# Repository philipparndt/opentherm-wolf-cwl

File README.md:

# Wolf CWL OpenTherm Decoder

Decoder tool for analyzing OpenTherm protocol communication between a BM remote control and a Wolf CWL ventilation/heat-recovery unit. Built to reverse-engineer the protocol for building a custom ESP32-based controller.

## Usage

```bash
# Default: human-readable deduplicated output
decode <file.sal|file.csv>

# Verbose: raw hex, parity, bit-timing analysis
decode <file> --verbose

# Diff: compare two captures side by side, highlights changes
decode diff <baseline.sal> <changed.sal>
```

Supports Saleae Logic 2 captures (`.sal`) and CSV exports (`.csv`). SAL files are significantly faster to process.

## Findings

### Control Summary

Everything needed to control the Wolf CWL via OpenTherm:

| Function | Method |
|----------|--------|
| **Ventilation level** | Write-Data to ID 71, value 0-3 |
| **Bypass open** | Set bit 1 in HI byte of ID 70 Read-Data request |
| **Bypass close** | Clear bit 1 in HI byte of ID 70 Read-Data request |
| **Filter reset** | Set bit 4 in HI byte of ID 70 Read-Data request (reset filter timer after replacement) |
| **Read temperatures** | Read-Data ID 80 (supply inlet), ID 82 (exhaust inlet) |
| **Read ventilation %** | Read-Data ID 77 |
| **Read bypass state** | Check `ventilation` bit (bit 1 HI byte) in ID 70 response |
| **Read fault status** | ID 72 (`Fault flags/code V/H`) — the HI-byte `fault` bit in ID 70 is *not* reliable on Wolf CWL, see notes below |
| **Read filter status** | Check **bit 5 of the LO byte** in ID 70 response (Wolf OEM use of a spec-reserved slave-status bit; the response HI byte is only an echo of the master flags) |

### Supported OpenTherm Data IDs

The Wolf CWL (tested with CWL Excellent, BM remote control as master) responds to the following data IDs:

| Data ID | Name | Type | Direction | Description |
|---------|------|------|-----------|-------------|
| 2 | Master configuration | config/member-id | Write | Master flags=0x00, member-id=18 |
| 70 | Status V/H | flag8 | Read | Bidirectional: master sends control flags, slave returns status |
| 71 | Control setpoint V/H | u8 | Write | Ventilation level (0-3) |
| 72 | Fault flags/code V/H | flag8 | Read | Fault flags + OEM fault code |
| 74 | Config/member-ID V/H | config/member-id | Read | Slave flags=0x07, member-id=0 |
| 77 | Relative ventilation | u8 (%) | Read | Current ventilation percentage |
| 80 | Supply inlet temperature | f8.8 (°C) | Read | Fresh air intake temperature |
| 82 | Exhaust inlet temperature | f8.8 (°C) | Read | Room exhaust temperature |
| 89 | TSP index/value V/H | tsp | Read | Transparent Slave Parameters (see below) |
| 126 | Master product version | version | Write | type=18 version=2 |
| 127 | Slave product version | version | Read | type=0 version=0 (CWL does not respond) |

### Status V/H (ID 70) — Bidirectional Control

The Status V/H exchange carries control flags in **both directions**. This is the key mechanism for bypass control.

**Master → Slave (HI byte of Read-Data request):**

| Bit | Name | Description |
|-----|------|-------------|
| 0 | ch | Central heating / ventilation enable |
| 1 | **bypass** | **Bypass damper control: 1=open, 0=closed** |
| 2 | cooling | Cooling enable (if cooling register installed) |
| 3 | dhw | DHW enable |
| 4 | filter | Filter timer reset (set briefly after filter replacement) |
| 5 | diag | Diagnostics request |

**Slave → Master (Read-Ack response):**

The **HI byte of the Read-Ack is an echo of the master status flags** from the request — it carries no slave state. (Earlier revisions of this document interpreted it as a slave status byte and described a "permanently latched fault bit"; that was our own always-set ventilation-enable bit coming back.)

The actual slave status is the **LO byte**, laid out as in the OpenTherm V/H spec:

| Bit | Name | Description |
|-----|------|-------------|
| 0 | fault | Fault indication |
| 1 | ventilation | Ventilation mode active |
| 2 | bypass | Bypass status (1 = open) |
| 3 | bypass auto | Bypass automatic mode |
| 4 | free vent | Free ventilation status |
| 5 | **filter** | **Filter replacement required (1 = service due, 0 = OK).** Reserved in the spec; used by Wolf (Brink Renovent / Viessmann Vitovent OEM siblings) as the filter-check bit. |
| 6 | diag | Diagnostic indication |

Bit 5 was confirmed in `FIL_CLEAN.sal`, which captures the live transition during a filter-reset: LO went from `0x26` → `0x06` (bit 5 cleared) while HI stayed at `0x03` and ID 72 (Fault flags/code) stayed at `0x0000` throughout.

> **Do not derive filter status from ID 72.** An OEM fault code of 6 was once assumed to mean "filter dirty" (FIL2 hypothesis), but a live unit was observed reporting ID 72 = `0x0006` together with LO bit 6 (diagnostic indication) while the filter was clean and the CWL display showed no FIL — code 6 is a diagnostic status code, not the filter message. LO bit 5 is the only reliable filter signal.

The bypass is controlled by setting/clearing **bit 1 of the HI byte** in every Status V/H request; the actual damper state is reported in LO bit 2 (and TSP 54).

### Ventilation Level Control

Ventilation level is controlled via **Data ID 71** (Control setpoint V/H). The mapping is:

| Setpoint value | Mode | Relative ventilation (ID 77) |
|---------------|------|------------------------------|
| 0 | Off | 0% |
| 1 | Reduced | 51% |
| 2 | Normal | 67% |
| 3 | Party | 100% |

The `fault` bit in Status V/H (ID 70) may toggle briefly during mode transitions. This appears to be a transient state, not an actual fault indication.

### TSP Register Map

The BM remote cycles through TSP registers via Data ID 89, reading one index per polling cycle (~11 seconds per cycle). A full TSP scan takes approximately 5-6 minutes (31 indices).

TSP values did **not** change when switching ventilation levels or toggling bypass. Ventilation is controlled via ID 71, bypass via ID 70. TSPs hold configuration and live diagnostic data.

The Wolf CWL is OEM-identical to the **Brink Renovent HR** and **Viessmann Vitovent 300**. The TSP register map from the [Brink Renovent OpenTherm project](https://github.com/raf1000/brink_openhab) applies directly.

Many indices come in even/odd pairs for 16-bit values (even=LO, odd=HI byte).

#### Airflow Configuration (m³/h)

| TSP Index | Brink name | Value | Description |
|-----------|------------|-------|-------------|
| 0, 1 | U1 | 100, 0 | Airflow rate step 1 (Reduced): **100 m³/h** |
| 2, 3 | U2 | 130, 0 | Airflow rate step 2 (Normal): **130 m³/h** |
| 4, 5 | U3 | 195, 0 | Airflow rate step 3 (Party): **195 m³/h** |

#### Bypass & Temperature Settings

| TSP Index | Brink name | Value | Description |
|-----------|------------|-------|-------------|
| 6 | U4 | 20 | Bypass min. outdoor temp (value ÷ 2 = °C → **10 °C**). Bypass only opens when outdoor air ≥ this temperature. |
| 7 | U5 | 44 | Bypass min. indoor temp (value ÷ 2 = °C → **22 °C**). Bypass only opens when indoor air ≥ this temperature. |

#### Configuration Parameters

| TSP Index | Brink name | Value | Description |
|-----------|------------|-------|-------------|
| 11 | I1 | 100 | Fixed imbalance (value shifted by 100, so 100 = **0% imbalance**) |
| 17 | I7 | 1 | Pressure control / fan mode setting |
| 18 | I8 | 1 | Bypass configuration |
| 19 | I9 | 2 | Hysteresis / preheater setting |
| 20 | I10 | 0 | Additional config |
| 23 | I13 | 1 | Filter message setting |
| 24 | I14 | 0 | PCB configuration |
| 48, 49 | P18 | 193, 0 | Device/PCB config flags |

#### Live / Status Values (read-only, change during operation)

| TSP Index | Brink name | Value range | Description |
|-----------|------------|-------------|-------------|
| 52, 53 | CurrentVol | 100-130, 0 | Current outlet volume **[m³/h]** |
| 54 | BypassStatus | 1 | Bypass valve position (0=shut, 1=auto, 2=open?) |
| 55 | TempAtmo | 114-118 | Atmospheric temperature (value − 100 = °C, so 114 → **14 °C**) |
| 56 | TempIndoors | 121 | Indoor temperature (value − 100 = °C, so 121 → **21 °C**) |
| 60, 61 | — | 0-130, 0 | Changes within captures — possibly supply/exhaust flow |
| 62, 63 | CurrentOutputVol | 100-113, 0 | Current output volume **[m³/h]** |
| 64, 65 | CPID | 20-215, 0-1 | Input duct pressure **[Pa]** |
| 66, 67 | CPOD | 196-255, 0 | Output duct pressure **[Pa]** |
| 68 | FrostStatus | 0 | Frost protection status (0 = no frost) |

### Data IDs to Probe

The BM remote only polls a subset of the available V/H data IDs. The following IDs are defined in the OpenTherm V/H spec and may be supported by the CWL, but have not been tested yet. Probe these with the ESP32 firmware to discover additional sensors:

| Data ID | Name | Type | Notes |
|---------|------|------|-------|
| 78 | Relative humidity exhaust | u8 (%) | Humidity sensor (if installed) |
| 79 | CO2 level exhaust | u16 (ppm) | CO2/VOC sensor (if installed) |
| 81 | Supply outlet temperature | f8.8 (°C) | Temperature after heat recovery |
| 83 | Exhaust outlet temperature | f8.8 (°C) | Temperature after heat recovery |
| 84 | Exhaust fan speed | u16 (rpm) | Fan speed diagnostics |
| 85 | Supply fan speed | u16 (rpm) | Fan speed diagnostics |
| 87 | Nominal ventilation value | u8 | Configured nominal airflow |
| 88 | TSP count V/H | u8 | Total number of TSP registers supported |

If the CWL supports a data ID, it will respond with Read-Ack. If not, it will either not respond or send Unknown-DataId.

### Polling Cycle

The BM remote polls the CWL in a fixed cycle of approximately 11 seconds containing:

1. Master configuration (ID 2) — Write-Data
2. Status V/H (ID 70) — Read-Data with master control flags
3. Control setpoint V/H (ID 71) — Write-Data
4. Config/member-ID V/H (ID 74) — Read-Data
5. Relative ventilation (ID 77) — Read-Data
6. Supply inlet temperature (ID 80) — Read-Data
7. Exhaust inlet temperature (ID 82) — Read-Data
8. Master product version (ID 126) — Write-Data
9. Slave product version (ID 127) — Read-Data (no response from CWL)
10. TSP index/value V/H (ID 89) — Read-Data, rotates through different index each cycle
11. Fault flags/code V/H (ID 72) — Read-Data (sometimes included)

## ESP32 Firmware Guide

The firmware serves a web UI with live status and a 24 h history view — supply/exhaust temperatures, indoor/outdoor humidity and enthalpy, bypass state, and ventilation level changes annotated with the reason for each switch:

### Minimal Polling Loop

To replicate the BM's communication, the ESP32 firmware should send these requests in a loop (~1 second between each):

```
1. Write-Data  ID=2   value=0x0012        (master config: member-id=18)
2. Read-Data   ID=70  value=0x0N00        (status: HI byte = control flags, N = bypass bit)
3. Write-Data  ID=71  value=0x000L        (ventilation level: L = 0-3)
4. Read-Data   ID=74  value=0x0000        (read config/member-id)
5. Read-Data   ID=77  value=0x0000        (read relative ventilation %)
6. Read-Data   ID=80  value=0x0000        (read supply inlet temp)
7. Read-Data   ID=82  value=0x0000        (read exhaust inlet temp)
8. Read-Data   ID=89  value=0xII00        (read TSP index II)
```

### Bypass Control

In step 2, set the HI byte of the request value:
- `0x0100` — bypass closed, ventilation enabled (ch=on)
- `0x0300` — bypass open, ventilation enabled (ch=on, bypass=on)

The slave response HI byte confirms the state:
- Bit 0: fault
- Bit 1: ventilation/bypass active

### Ventilation Levels

In step 3, set the LO byte:
- `0x0000` — Off (0%)
- `0x0001` — Reduced (51%)
- `0x0002` — Normal (67%)
- `0x0003` — Party (100%)

## Hardware

### Capture Setup (passive analysis)

- **Saleae Logic 2** analyzer tapping the OpenTherm bus between BM remote and CWL unit
- Analog capture at 1.5625 MHz sample rate
- OpenTherm signal: Manchester encoded at ~1000 baud
- Request (master→slave): ~10.8V peak
- Response (slave→master): ~7.3V peak

### Controller Hardware

- **DIYLess Master OpenTherm Shield** — handles OpenTherm electrical signaling
- **ESP32** (e.g. WeMos D1 mini ESP32) — runs custom firmware
- **[ihormelnyk/opentherm_library](https://github.com/ihormelnyk/opentherm_library)** — Arduino library for OpenTherm master communication

The DIYLess shield acts as the OpenTherm master, replacing the BM remote control. The ESP32 can then:
- Read all sensor values (temperatures, ventilation %, status, faults)
- Set ventilation level by writing to Data ID 71 (values 0-3)
- Control bypass via Status V/H (ID 70) master flags
- Read TSP registers for diagnostics
- Publish data via MQTT to Home Assistant (see [docs/mqtt-topics.md](docs/mqtt-topics.md) for the full topic reference)

### ESPHome Compatibility

The official ESPHome OpenTherm component does **not** support V/H (ventilation/heat-recovery) data IDs 70-91. It only supports boiler/heating control. A custom firmware is required for the Wolf CWL.

## Building

```bash
cd decode
go build -o decode .
```

Requires Go 1.26+.

## Schedules

Weekday schedule:
```
0:00 - 8:00 reduced
8:00 - 13:00 normal
13:00 - 15:00 reduced
15:00 - 18:00 normal
18:00 - 0:00 reduced
```

Weekend schedule:
```
0:00 - 10:00 reduced
10:00 - 13:00 normal
13:00 - 15:00 reduced
15:00 - 18:30 normal
```

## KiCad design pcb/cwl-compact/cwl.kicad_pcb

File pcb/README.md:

# Wolf CWL Controller — Shield PCB

Shield board that stacks on top of an [Olimex ESP32-POE](https://www.olimex.com/Products/IoT/ESP32/ESP32-POE/open-source-hardware) via the UEXT connector. Provides the OpenTherm interface, OLED display, and rotary encoder.

## UEXT Connector Pinout (ESP32-POE)

The [UEXT](https://www.olimex.com/Products/Modules/UEXT/) is a 10-pin 2x5 box header (2.54 mm pitch) providing I²C, SPI, and UART:

| UEXT Pin | Signal | ESP32 GPIO | Used For |
|----------|--------|------------|----------|
| 1  | 3.3V | —       | Power |
| 2  | GND  | —       | Ground |
| 3  | TXD  | GPIO 4  | OpenTherm TX (via SB3) |
| 4  | RXD  | GPIO 36 | OpenTherm RX (via SB4) |
| 5  | SCL  | GPIO 16 | OLED Display |
| 6  | SDA  | GPIO 13 | OLED Display |
| 7  | MISO | GPIO 15 | Encoder CLK |
| 8  | MOSI | GPIO 2  | Status LED |
| 9  | SCK  | GPIO 14 | Encoder DT |
| 10 | SS   | GPIO 5  | Encoder SW |

## Variants

| Variant | Project | Notes |
|---------|---------|-------|
| `cwl` (default) | `cwl/cwl.kicad_pro` | Main board. Melnyk-topology on-board OpenTherm front-end. Combined OLED footprint accepts either a 0.96″ or 1.3″ SH1106 module. |
| `cwl-diyless` | `cwl-diyless/cwl.kicad_pro` | Off-board OpenTherm interface via a DIYless D1-mini shield. Separate J3 / J3B footprints for the two OLED sizes. |

## Bill of Materials (`cwl`)

| Ref | Part | Value / Mfr P/N | Footprint | Symbol | Mouser # | Qty |
|-----|------|-----------------|-----------|--------|----------|-----|
| J1 | UEXT 2×5 IDC socket | HIF3FB-10DA-2.54DSA(69) (Hirose) | `IDC:IDC-Stecker_2x05_P2.54mm_Vertical` | `Connector_Generic:Conn_02x05_Odd_Even` | 798-HIF3FB10DA254D69 | 1 |
| J2 | Screw terminal, 2-pos 5.08 mm | MKDS 1,5/2-5,08 (Phoenix Contact) | `TerminalBlock_Phoenix:TerminalBlock_Phoenix_MKDS-1,5-2-5.08_1x02_P5.08mm_Horizontal` | `Connector:Conn_01x02_Pin` | 651-1729018 | 1 |
| J3 | OLED header (0.96″ + 1.3″ combined) | 4-pin header (use module's own header) | `SSD1306:128x64OLED-MountingHoles-Combined` | `Connector:Conn_01x04_Pin` | — | 1 |
| U1, U2 | Optocoupler, SOIC-4 | LTV-817S-B (Lite-On) | `Package_SO:SOP-4_7.5x4.1mm_P2.54mm` | `Isolator:PC817` | 859-LTV-817S-B | 2 |
| Q1 | PNP BJT, SOT-23 | BC858A or BC858B (Nexperia) | `Package_TO_SOT_SMD:SOT-23` | `Transistor_BJT:BC858` | 771-BC858A,215 | 1 |
| D1–D4 | Switching diode, SOD-323 | 1N4148WS (Vishay) | `Diode_SMD:D_SOD-323` | `Device:D` | 78-1N4148WS-HG3_A-08 | 4 |
| D5 | 4.7 V zener, SOD-123, 500 mW | BZT52C4V7 (Vishay) | `Diode_SMD:D_SOD-123` | `Device:D_Zener` | 78-BZT52C4V7-E3-08 | 1 |
| D6 | 15 V zener, SOD-123, 500 mW | BZT52C15 (Vishay) | `Diode_SMD:D_SOD-123` | `Device:D_Zener` | 78-BZT52C15-E3-08 | 1 |
| D7 | 4.3 V zener, SOD-123, 500 mW | BZT52C4V3 (Vishay) | `Diode_SMD:D_SOD-123` | `Device:D_Zener` | 78-BZT52C4V3-E3-08 | 1 |
| R1, R4 | 330 Ω, 0603, 1 % | RC0603FR-07330RL (Yageo) | `Resistor_SMD:R_0603_1608Metric` | `Device:R` | 603-RC0603FR-07330RL | 2 |
| R2 | 220 Ω, 0603, 1 % | RC0603FR-07220RL (Yageo) | `Resistor_SMD:R_0603_1608Metric` | `Device:R` | 603-RC0603FR-07220RL | 1 |
| R3 | 100 Ω, 0603, 1 % | RC0603FR-07100RL (Yageo) | `Resistor_SMD:R_0603_1608Metric` | `Device:R` | 603-RC0603FR-07100RL | 1 |
| R5 | 1.5 kΩ, 0603, 1 % | RC0603FR-071K5L (Yageo) | `Resistor_SMD:R_0603_1608Metric` | `Device:R` | 603-RC0603FR-071K5L | 1 |
| R6, R7 | 10 kΩ, 0603, 1 % | RC0603FR-0710KL (Yageo) | `Resistor_SMD:R_0603_1608Metric` | `Device:R` | 603-RC0603FR-0710KL | 2 |
| R8 | 1 kΩ, 0603, 1 % | RC0603FR-071KL (Yageo) | `Resistor_SMD:R_0603_1608Metric` | `Device:R` | 603-RC0603FR-071KL | 1 |
| SW1 | Rotary encoder w/ switch | EC12E2424407 (Alps Alpine) | `Rotary_Encoder:RotaryEncoder_Alps_EC12E-Switch_Vertical_H20mm` | `Device:RotaryEncoder_Switch` | — | 1 |
| LED1 | Green LED, 0805 | SML-LXT0805GW-TR (Lumex) | `LED_SMD:LED_0805_2012Metric` | `Device:LED` | 696-SML-LXT0805GW | 1 |
| MH1–MH4 | M3 mounting hole, GND-tied | — | `MountingHole:MountingHole_3.2mm_M3_Pad_Via` | `Mechanical:MountingHole_Pad` | — | 4 |
| SB3, SB4 | UEXT TX/RX → OT routing bridges (etched into board, no part) | — | `Jumper:SolderJumper-2_P1.3mm_Bridged_RoundedPad1.0x1.5mm` | `Jumper:SolderJumper_2_Bridged` | — | — |
| — | 0.96″ SH1106 OLED module, I²C, 4-pin | — | — | — | (Amazon / AliExpress) | 1 (pick one) |
| — | 1.3″ SH1106 OLED module, I²C, 4-pin | — | — | — | (Amazon / AliExpress) | 1 (pick one) |

## Build targets

```
make generate-3d      # regenerate the local STEP models in 3dmodels/
make export-stl-full  # full PCB assembly STL (VARIANT=cwl by default)
make export-stl-print # version with floating IDC socket for 3D printing
make export-stl-board # bare PCB only
make export-stl-parts # components only (no board)
make gerber           # Gerbers + drills (zipped)
make plot-pdf         # front + back assembly PDFs
make ibom             # Interactive HTML BOM (needs InteractiveHtmlBom plugin)
make clean            # remove generated artifacts
```

Set `VARIANT=cwl-diyless` to target the diyless project instead.

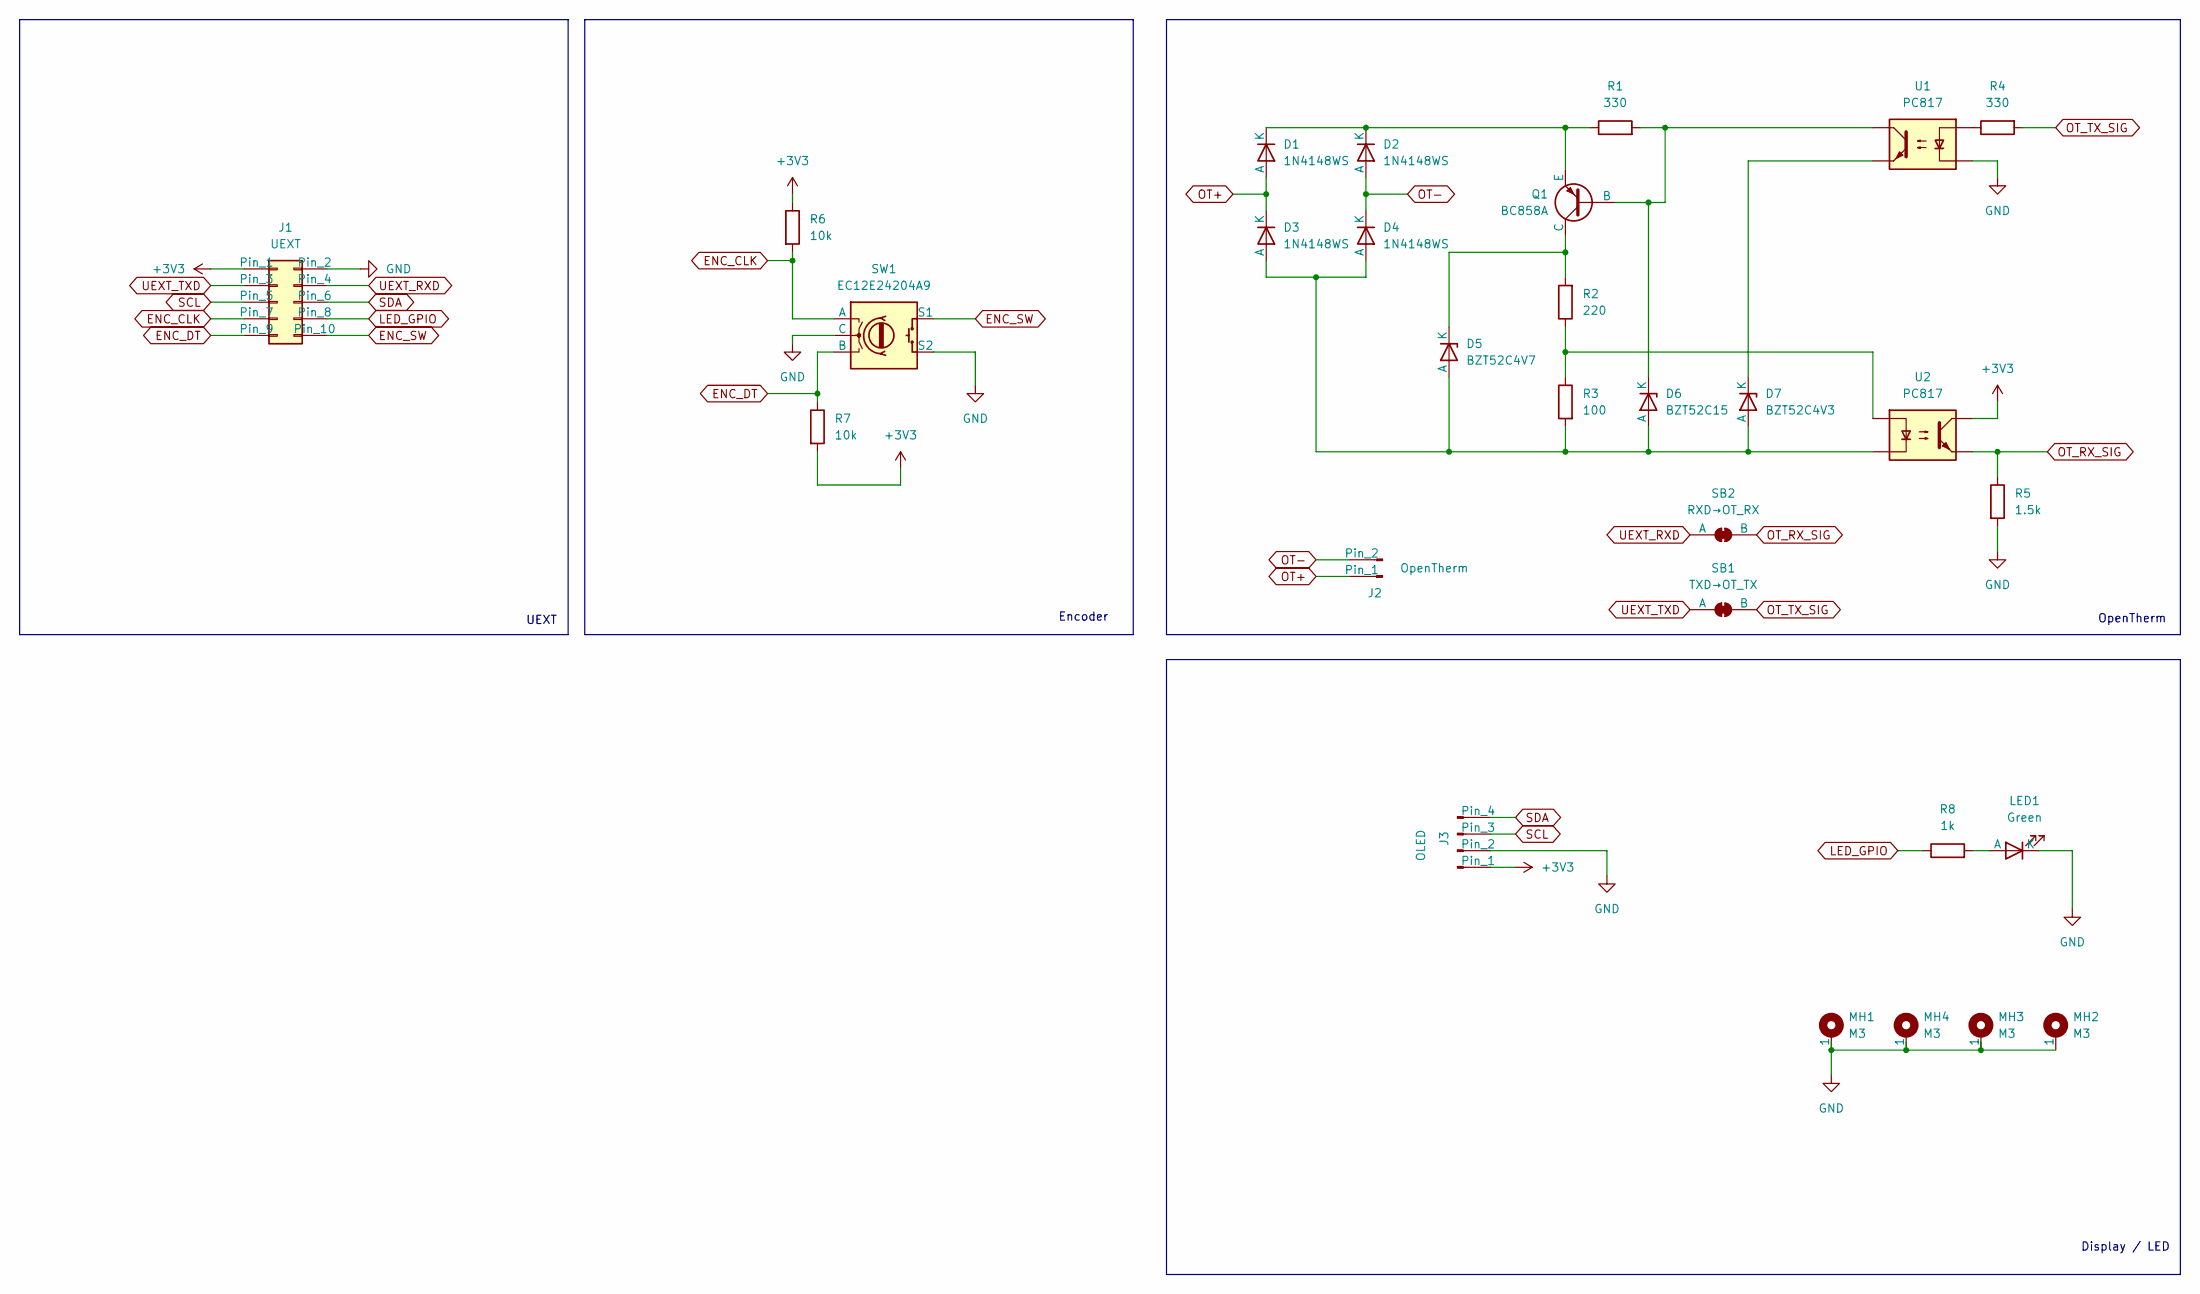
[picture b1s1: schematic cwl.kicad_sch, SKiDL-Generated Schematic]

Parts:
D1, D2, D3, D4: 1N4148WS; D_SOD-323
D5: BZT52C4V7; D_SOD-123
D6: BZT52C15; D_SOD-123
D7: BZT52C4V3; D_SOD-123
J1: UEXT; IDC-Stecker_2x05_P2.54mm_Vertical; LCSC C358738
J2: OpenTherm; TerminalBlock_Phoenix_MKDS-1,5-2-5.08_1x02_P5.08mm_Horizont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
J3: OLED; 128x64OLED-MountingHoles-Combined
LED1: Green; LED_0805_2012Metric; LCSC C2297
MH1, MH2, MH3, MH4: M3; MountingHole_3.2mm_M3_Pad_Via
Q1: BC858A; SOT-23
R1, R4: 330; R_0603_1608Metric; LCSC C23138
R2: 220; R_0603_1608Metric; LCSC C22962
R3: 100; R_0603_1608Metric; LCSC C22775
R5: 1.5k; R_0603_1608Metric; LCSC C22843
R6, R7: 10k; R_0603_1608Metric; LCSC C25804
R8: 1k; R_0603_1608Metric; LCSC C21190
SB1: TXD→OT_TX; SolderJumper-2_P1.3mm_Bridged_RoundedPad1.0x1.5mm
SB2: RXD→OT_RX; SolderJumper-2_P1.3mm_Bridged_RoundedPad1.0x1.5mm
SW1: EC12E24204A9; RotaryEncoder_Alps_EC12E-Switch_Vertical_H20mm
U1, U2: PC817; SOP-4_7.5x4.1mm_P2.54mm

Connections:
+3V3: J1.1, J3.1, R6.1, R7.2, U2.4
ENC_CLK: J1.7, R6.2, SW1.A
ENC_DT: J1.9, R7.1, SW1.B
ENC_SW: J1.10, SW1.S1
GND: J1.2, J3.2, LED1.1 (K), MH1.1 (1_1), MH2.1 (1_1), MH3.1 (1_1), MH4.1 (1_1), R5.2, SW1.C, SW1.MP, SW1.S2, U1.2
LED_GPIO: J1.8, R8.1
unnamed: D1.1 (K), D2.1 (K), Q1.2 (E), R1.1
unnamed: D3.2 (A), D4.2 (A), D5.2 (A), D6.2 (A), D7.2 (A), R3.2, U2.2
unnamed: D5.1 (K), Q1.3 (C), R2.2
unnamed: D6.1 (K), Q1.1 (B), R1.2, U1.4
unnamed: D7.1 (K), U1.3
unnamed: LED1.2 (A), R8.2
unnamed: R2.1, R3.1, U2.1
unnamed: R4.1, U1.1
OT+: D1.2 (A), D3.1 (K), J2.1
OT-: D2.2 (A), D4.1 (K), J2.2
OT_RX_SIG: R5.1, SB2.2 (B), U2.3
OT_TX_SIG: R4.2, SB1.2 (B)
SCL: J1.5, J3.3
SDA: J1.6, J3.4
UEXT_RXD: J1.4, SB2.1 (A)
UEXT_TXD: J1.3, SB1.1 (A)

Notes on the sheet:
UEXT
OpenTherm
Display / LED
Encoder

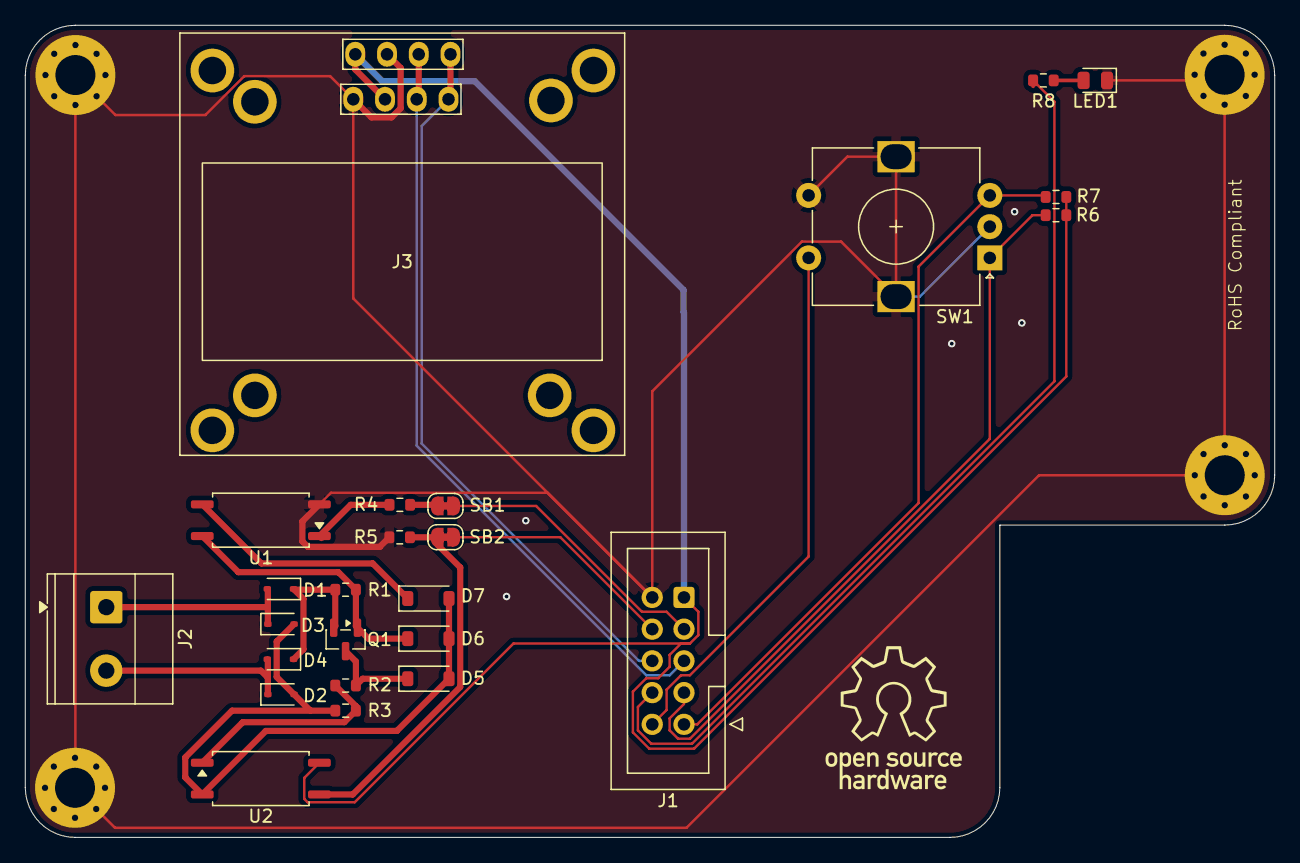
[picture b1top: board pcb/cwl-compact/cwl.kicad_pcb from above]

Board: 2 copper layers, 100.0 x 65.0 mm, 29 parts (0 on the bottom side), 22 nets.

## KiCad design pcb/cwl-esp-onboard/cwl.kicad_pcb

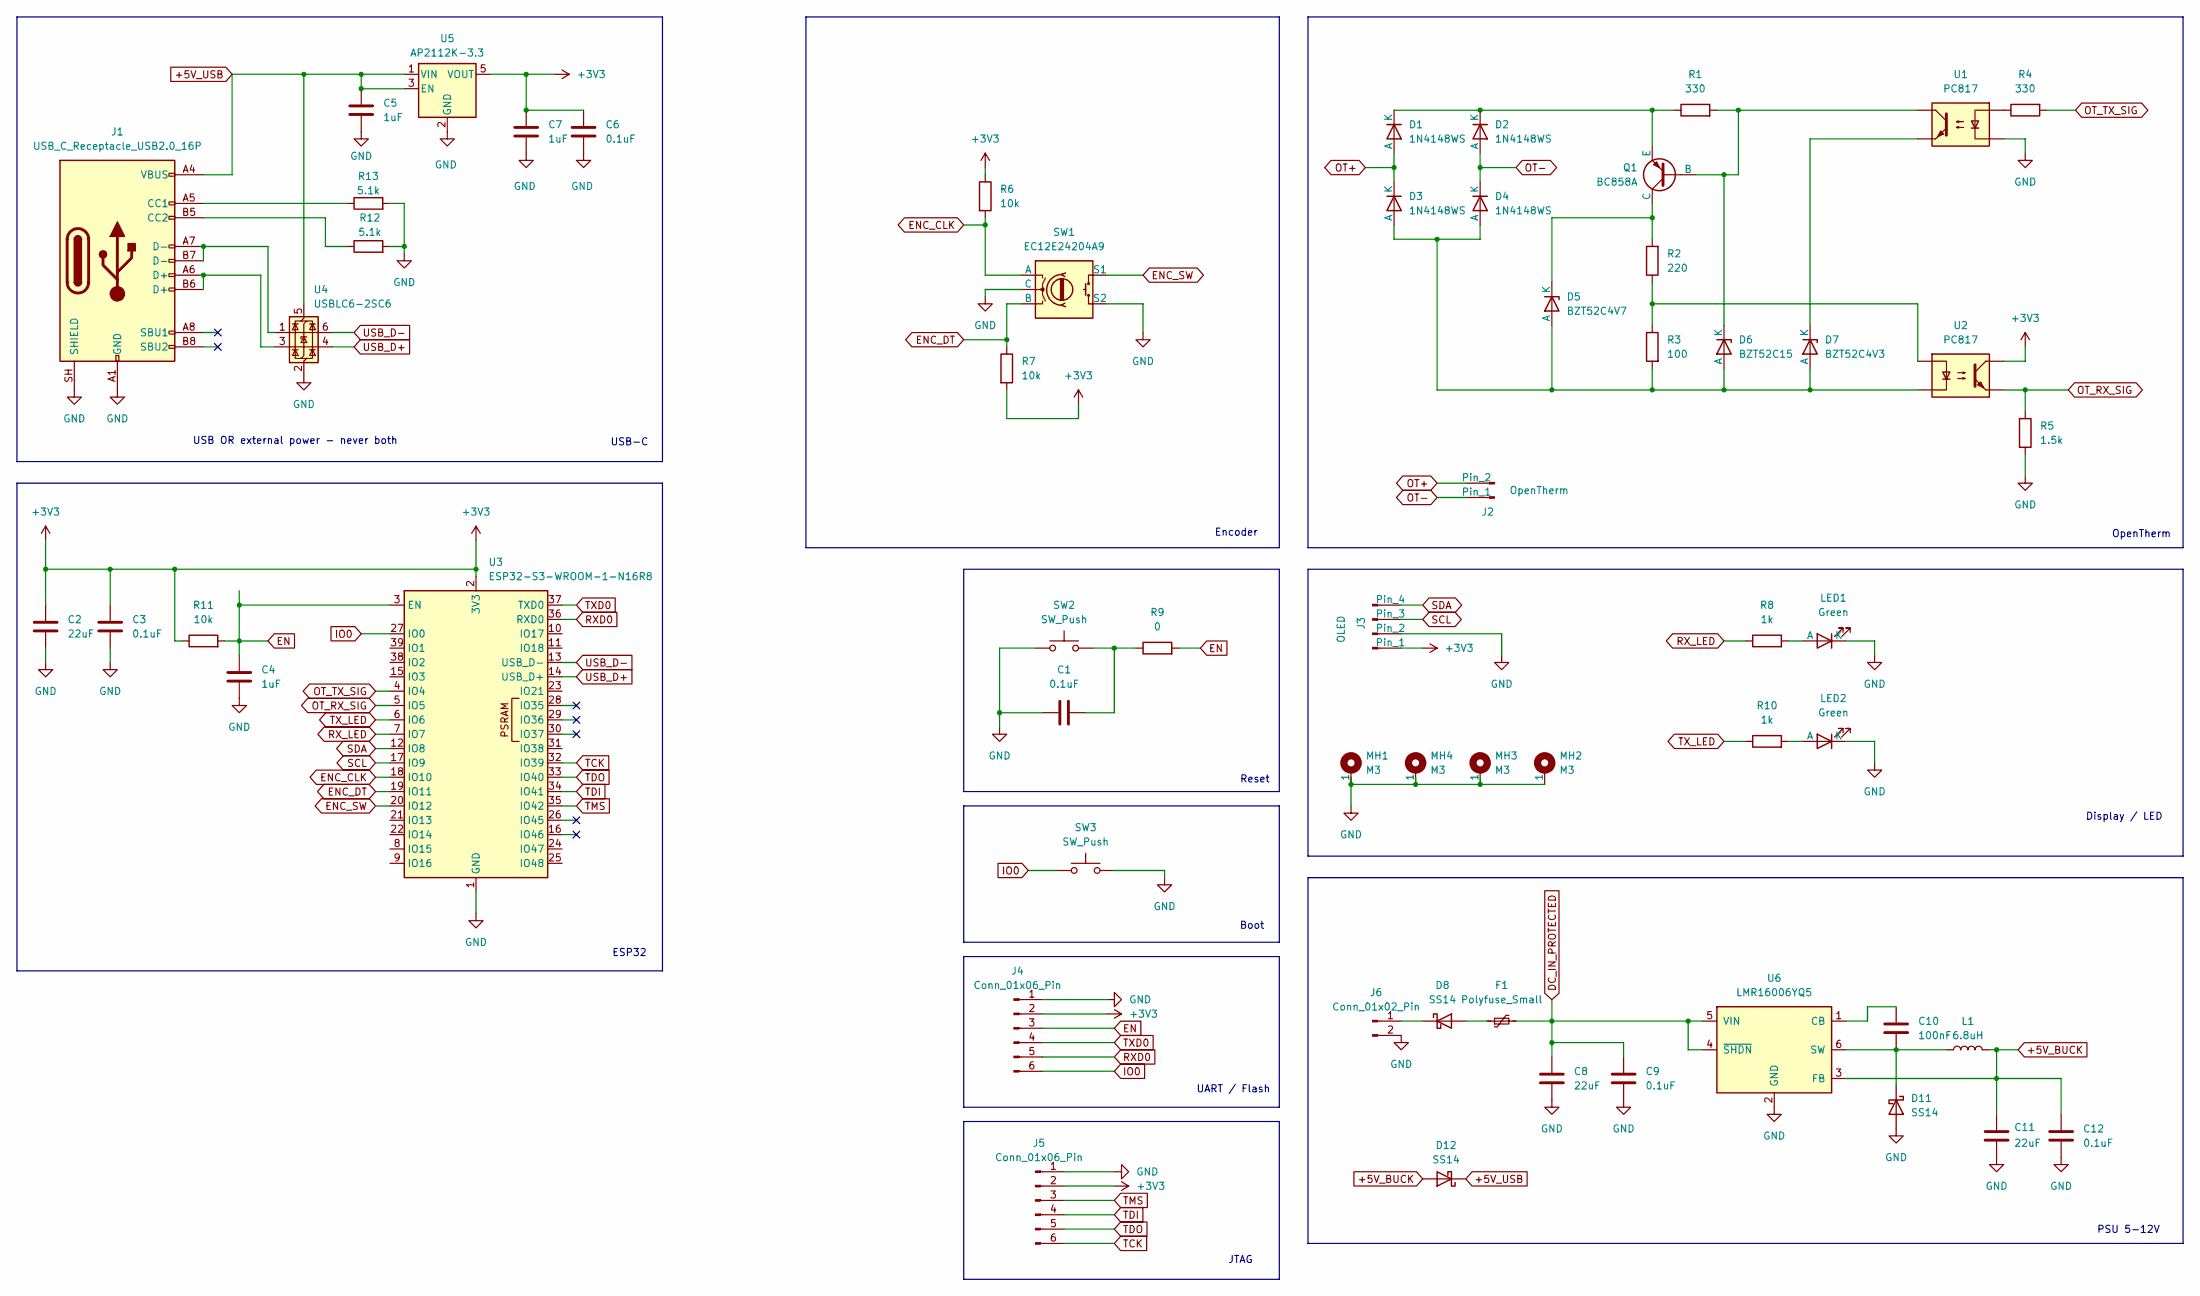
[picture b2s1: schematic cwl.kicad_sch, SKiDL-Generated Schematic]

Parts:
C1, C3, C6, C9, C12: 0.1uF; C_0402_1005Metric
C2, C8, C11: 22uF; C_1210_3225Metric
C4, C5, C7: 1uF; C_0402_1005Metric
C10: 100nF; C_0402_1005Metric
D1, D2, D3, D4: 1N4148WS; D_SOD-323
D5: BZT52C4V7; D_SOD-123
D6: BZT52C15; D_SOD-123
D7: BZT52C4V3; D_SOD-123
D8, D11, D12: SS14; D_SMA
F1: Polyfuse_Small; Fuse_1812_4532Metric
J1: USB_C_Receptacle_USB2.0_16P; USB_C_Receptacle_HRO_TYPE-C-31-M-12
J2: OpenTherm; TerminalBlock_Phoenix_MKDS-1,5-2-5.08_1x02_P5.08mm_Horizont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
J3: OLED; 128x64OLED-MountingHoles-Combined
J4: Conn_01x06_Pin; PinHeader_1x06_P2.54mm_Vertical
J5: Conn_01x06_Pin; PinHeader_1x06_P1.27mm_Vertical_SMD_Pin1Left
J6: Conn_01x02_Pin; TerminalBlock_Phoenix_MKDS-1,5-2-5.08_1x02_P5.08mm_Horizont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
L1: 6.8uH; L_6.3x6.3_H3
LED1, LED2: Green; LED_0805_2012Metric
MH1, MH2, MH3, MH4: M3; MountingHole_3.2mm_M3_Pad_Via
Q1: BC858A; SOT-23
R1, R4: 330; R_0603_1608Metric
R2: 220; R_0603_1608Metric
R3: 100; R_0603_1608Metric
R5: 1.5k; R_0603_1608Metric
R6, R7: 10k; R_0603_1608Metric
R8, R10: 1k; R_0603_1608Metric
R9: 0; R_0402_1005Metric
R11: 10k; R_0402_1005Metric
R12, R13: 5.1k; R_0402_1005Metric
SW1: EC12E24204A9; RotaryEncoder_Alps_EC12E-Switch_Vertical_H20mm
SW2, SW3: SW_Push; SW_SPST_TL3342
U1, U2: PC817; SOP-4_7.5x4.1mm_P2.54mm
U3: ESP32-S3-WROOM-1-N16R8; ESP32-S3-WROOM-1
U4: USBLC6-2SC6; SOT-23-6
U5: AP2112K-3.3; SOT-23-5
U6: LMR16006YQ5; SOT-23-6

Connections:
+3V3: C2.1, C3.1, C6.1, C7.1, J3.1, J4.2, J5.2, R6.1, R7.2, R11.1, U2.4, U3.2 (3V3), U5.5 (VOUT); also elsewhere on the board
+5V_BUCK: C11.1, C12.1, D12.2 (A), L1.2, U6.3 (FB)
+5V_USB: C5.1, D12.1 (K), J1.A4 (VBUS), J1.A9 (VBUS), J1.B4 (VBUS), J1.B9 (VBUS), U4.5 (VBUS), U5.1 (VIN), U5.3 (EN)
EN: C4.2, J4.3, R9.2, R11.2, U3.3 (EN)
ENC_CLK: R6.2, SW1.A, U3.18 (IO10); also elsewhere on the board
ENC_DT: R7.1, SW1.B, U3.19 (IO11); also elsewhere on the board
ENC_SW: SW1.S1, U3.20 (IO12); also elsewhere on the board
IO0: J4.6, SW3.1, U3.27 (IO0)
unnamed: C1.2, R9.1, SW2.2
unnamed: D1.1 (K), D2.1 (K), Q1.2 (E), R1.1
unnamed: D3.2 (A), D4.2 (A), D5.2 (A), D6.2 (A), D7.2 (A), R3.2, U2.2
unnamed: D5.1 (K), Q1.3 (C), R2.2
unnamed: D6.1 (K), Q1.1 (B), R1.2, U1.4
unnamed: D7.1 (K), U1.3
unnamed: D8.2 (A), F1.1
unnamed: D8.1 (K), J6.1
unnamed: J1.A5 (CC1), R13.1
unnamed: J1.B5 (CC2), R12.1
unnamed: J1.A6 (D+), J1.B6 (D+), U4.3 (I/O2)
unnamed: J1.A7 (D-), J1.B7 (D-), U4.1 (I/O1)
unnamed: LED1.2 (A), R8.2
unnamed: LED2.2 (A), R10.2
unnamed: R2.1, R3.1, U2.1
unnamed: R4.1, U1.1
OT+: D1.2 (A), D3.1 (K), J2.2
OT-: D2.2 (A), D4.1 (K), J2.1
OT_RX_SIG: R5.1, U2.3, U3.5 (IO5); also elsewhere on the board
OT_TX_SIG: R4.2, U3.4 (IO4); also elsewhere on the board
RXD0: J4.5, U3.36 (RXD0)
RX_LED: R8.1, U3.7 (IO7)
SCL: J3.3, U3.17 (IO9); also elsewhere on the board
SDA: J3.4, U3.12 (IO8); also elsewhere on the board
TCK: J5.6, U3.32 (IO39)
TDI: J5.4, U3.34 (IO41)
TDO: J5.5, U3.33 (IO40)
TMS: J5.3, U3.35 (IO42)
TXD0: J4.4, U3.37 (TXD0)
TX_LED: R10.1, U3.6 (IO6)
USB_D+: U3.14 (USB_D+), U4.4 (I/O2)
USB_D-: U3.13 (USB_D-), U4.6 (I/O1)

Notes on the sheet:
Boot
USB-C
Reset
PSU 5-12V
OpenTherm
UART / Flash
ESP32
JTAG
Display / LED
Encoder
USB OR external power - never both

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
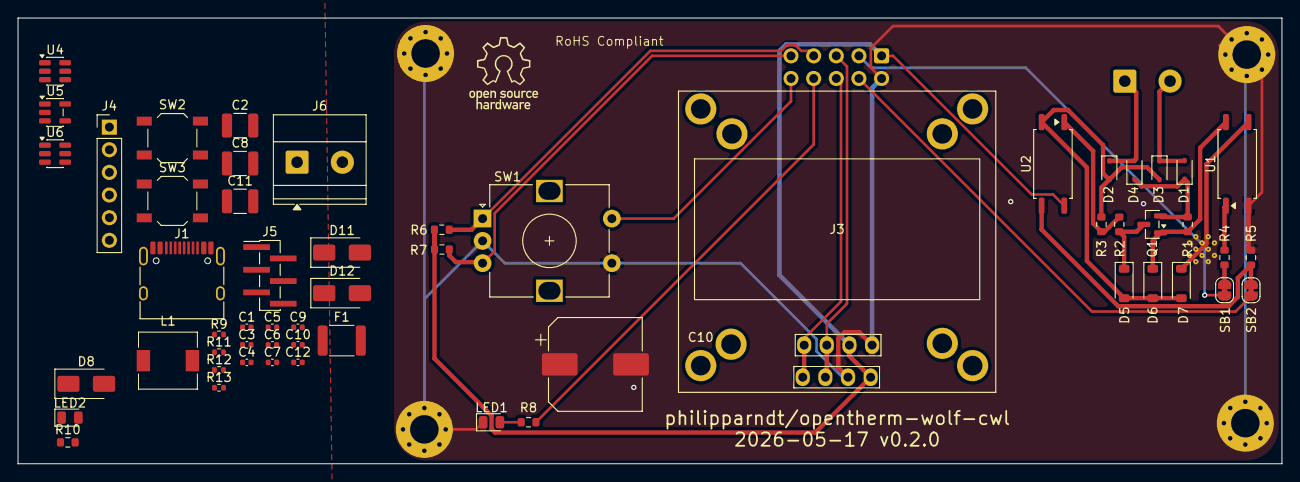
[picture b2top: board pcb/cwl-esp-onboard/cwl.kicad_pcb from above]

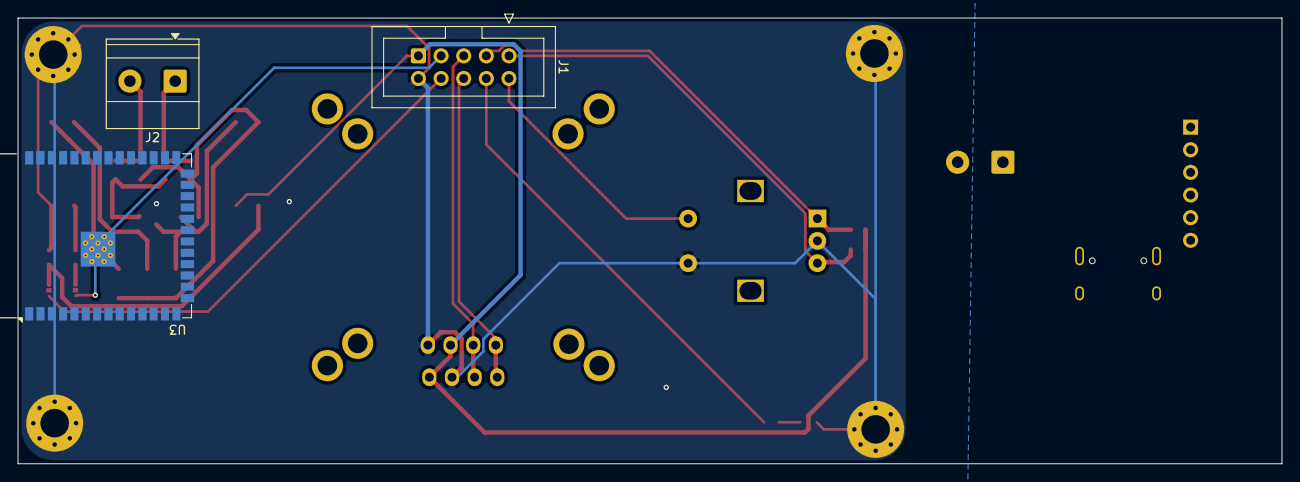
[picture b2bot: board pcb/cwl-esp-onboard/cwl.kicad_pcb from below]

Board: 2 copper layers, 141.8 x 50.0 mm, 63 parts (3 on the bottom side), 46 nets.

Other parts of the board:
C10#2: 100nF; C_0402_1005Metric
J1#2: UEXT; IDC-Stecker_2x05_P2.54mm_Vertical
SB1: TXD→OT_TX; SolderJumper-2_P1.3mm_Bridged_RoundedPad1.0x1.5mm
SB2: RXD→OT_RX; SolderJumper-2_P1.3mm_Bridged_RoundedPad1.0x1.5mm

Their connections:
+3V3: J1#2.1; also elsewhere on the board
ENC_CLK: J1#2.7; also elsewhere on the board
ENC_DT: J1#2.9; also elsewhere on the board
ENC_SW: J1#2.10; also elsewhere on the board
OT_RX_SIG: SB2.2 (B); also elsewhere on the board
OT_TX_SIG: SB1.2 (B); also elsewhere on the board
SCL: J1#2.5; also elsewhere on the board
SDA: J1#2.6; also elsewhere on the board
UEXT_RXD: J1#2.4, SB2.1 (A)
UEXT_TXD: J1#2.3, SB1.1 (A)

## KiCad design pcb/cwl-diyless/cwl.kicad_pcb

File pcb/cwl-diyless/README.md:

# Wolf CWL Shield — `cwl-diyless` variant

DIYless-based variant of the shield: no on-board OpenTherm circuit, a soldered-on DIYless D1 mini OT shield instead, and both 0.96" (J3) and 1.3" (J3B) OLED footprints on the same board (populate one).

## What's on this board

| Ref       | Component                                  | Notes                                                                 |
|-----------|--------------------------------------------|-----------------------------------------------------------------------|
| J1        | UEXT 2×5 IDC socket (Olimex stack)         | Same as the original variant                                          |
| J3        | OLED 0.96" SSD1306 footprint               | Pinout pad 1→4: GND, VCC, SCL, SDA                                    |
| J3B       | OLED 1.3" SH1106 footprint                 | Pinout pad 1→4: VDD, GND, SCK, SDA — populate **either J3 or J3B**    |
| J4        | EXT GPIO breakout (GPIO 4 / GPIO 36 / GND) | JST XH 3-pin                                                          |
| J5        | Aux breakout (3V3 / GND / TXD / RXD)       | JST XH 4-pin — useful for external logic-probe access                 |
| J6        | DIYless D1 mini left header (1×8)          | Pins NC except P8 = 3V3                                               |
| J7        | DIYless D1 mini right header (1×8)         | P3 = D1 (OT TX), P4 = D2 (OT RX), P7 = GND, P8 = 5V (NC by default)   |
| J8        | UEXT debug 1×10 pin header                 | All 10 UEXT signals broken out for scope/LA hook-up                   |
| SW1       | Alps EC12E rotary encoder + switch         | Same as the original variant                                          |
| LED1 + R8 | Status LED + 1 kΩ series resistor          | Same as the original variant                                          |
| MH1–MH4   | M3 mounting holes (GND-stitched)           |                                                                       |

**Omitted vs. `cwl/`:** R1–R5, R8 (kept), U1, U2, Q1, D1–D5 (on-board OT optocoupler interface), J2 (screw terminal), SB1–SB4 (OT routing solder bridges). The DIYless shield carries all of those functions and its own bus terminal.

## D1 mini layout reminder for the PCB editor

J6 (left) and J7 (right) are placed at the standard D1 mini header spacing — **22.86 mm (0.9") between row centerlines**, both rows running parallel along the long axis of the shield. The shield's 16 male pins drop straight into the PTH pads.

The five pins that carry actual signal are:

```
   J6 (left)             J7 (right)
   ┌───┐                ┌───┐
   │ 1 │ RST            │ 1 │ TX
   │ 2 │ A0             │ 2 │ RX
   │ 3 │ D0             │ 3 │ D1   →  ot_tx_sig (UEXT TXD, GPIO 4)
   │ 4 │ D5             │ 4 │ D2   →  ot_rx_sig (UEXT RXD, GPIO 36)
   │ 5 │ D6             │ 5 │ D3
   │ 6 │ D7             │ 6 │ D4
   │ 7 │ D8             │ 7 │ GND
   │ 8 │ 3V3            │ 8 │ 5V   (leave NC, or jumper-wire externally if
   └───┘                └───┘       your DIYless revision needs 5V on Vin)
```

## Workflow

```bash
# Generate the netlist
make generate VARIANT=cwl-diyless

# In KiCad: create a new project at pcb/cwl-diyless/cwl.kicad_pro,
#          open the PCB editor, File → Import Netlist → wolf-cwl-shield-cwl-diyless.net,
#          place components (use the D1 mini spacing above for J6/J7),
#          route, then back to the top level for Gerbers:

make gerber VARIANT=cwl-diyless
make plot-pdf VARIANT=cwl-diyless
```

## Firmware

Use the existing `../../esp32/` build (Olimex target). Flash with `make prod-wifi` (or `make dev-wifi` for simulated OT). No firmware changes needed — pin assignments via `ot-ext` already match GPIO 4 / GPIO 36.

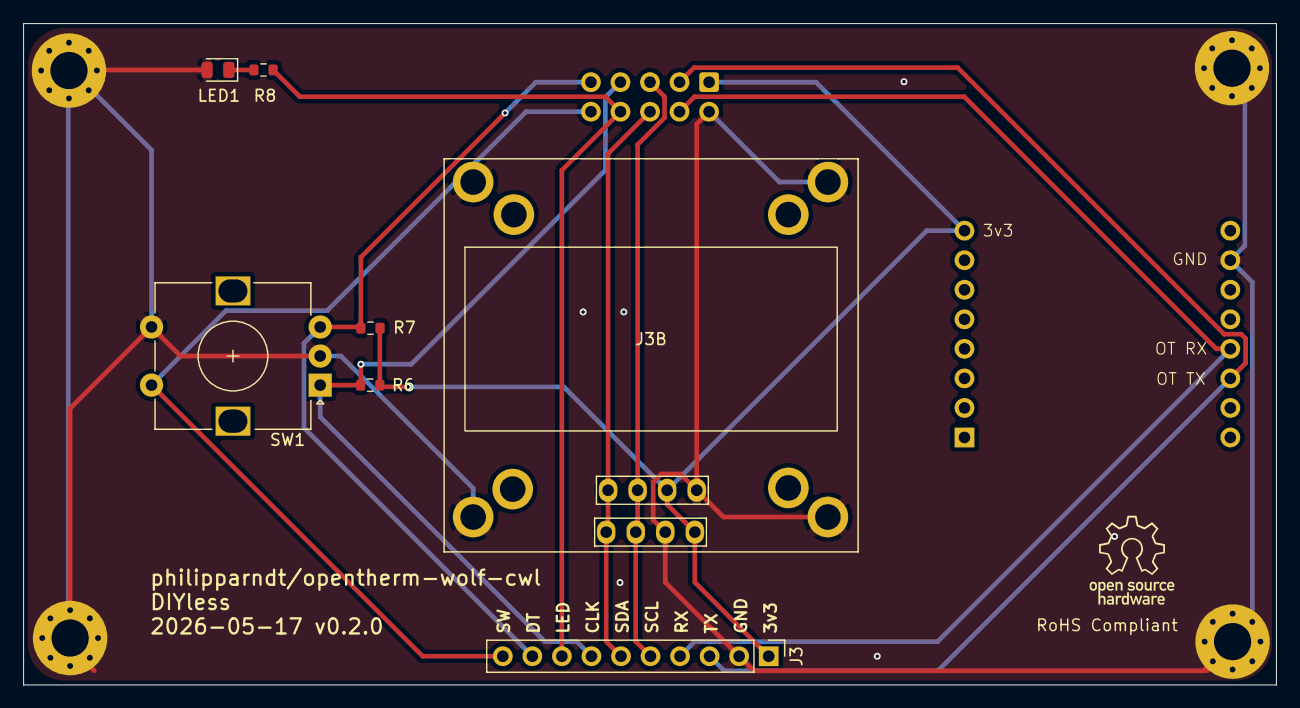
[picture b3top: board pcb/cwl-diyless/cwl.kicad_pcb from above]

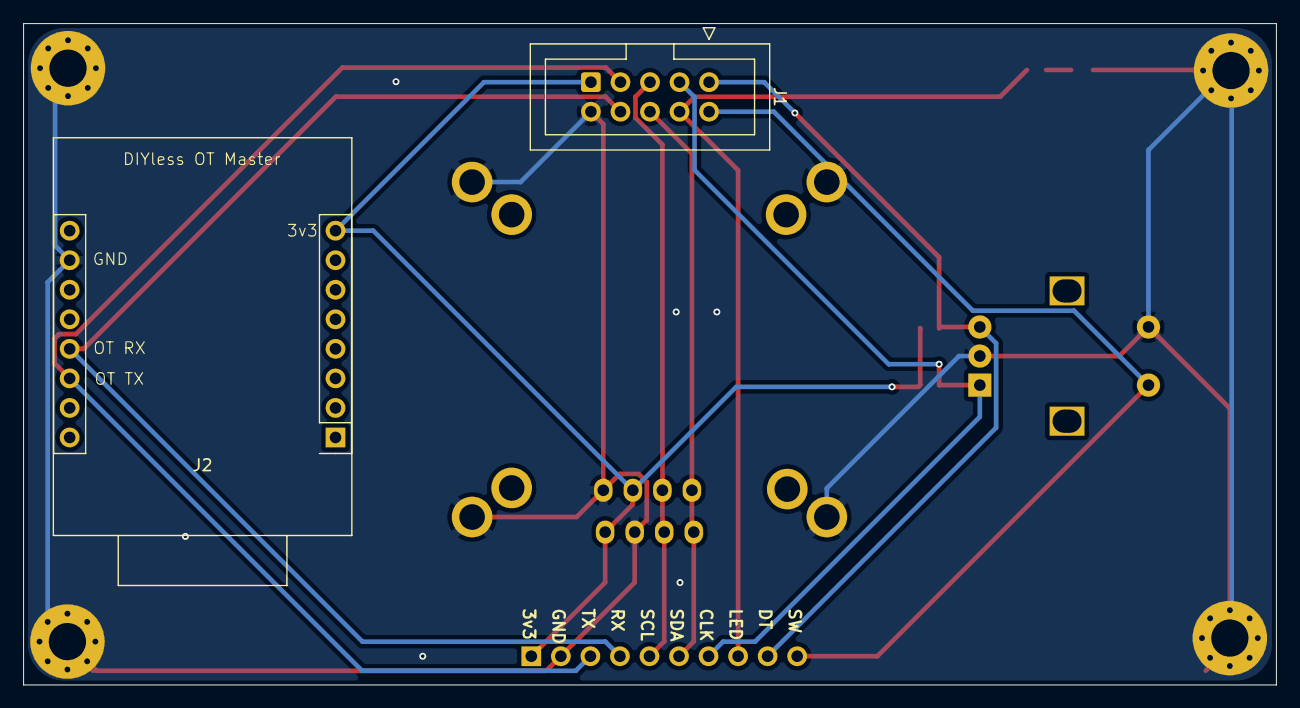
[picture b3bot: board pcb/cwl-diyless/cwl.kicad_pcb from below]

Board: 2 copper layers, 107.7 x 56.9 mm, 13 parts (2 on the bottom side), 11 nets.

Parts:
J1: UEXT; IDC-Stecker_2x05_P2.54mm_Vertical
J2: D1mini; D1_Mini_2x08_P2.54mm
J3: UEXT_DBG; PinHeader_1x10_P2.54mm_Vertical
J3B: OLED_1.3; 128x64OLED-MountingHoles-Combined
LED1: Green; LED_0805_2012Metric
MH1, MH2, MH3, MH4: M3; MountingHole_3.2mm_M3_Pad_Via
R6, R7: 10k; R_0603_1608Metric
R8: 1k; R_0603_1608Metric
SW1: EC12E24204A9; RotaryEncoder_Alps_EC12E-Switch_Vertical_H20mm

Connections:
+3V3: J1.1, J2.8, J3.1, J3B.1, R6.2, R7.2
ENC_CLK: J1.7, J3.7, R6.1, SW1.A
ENC_DT: J1.9, J3.9, R7.1, SW1.B
ENC_SW: J1.10, J3.10, SW1.S1
GND: J1.2, J2.15, J3.2, J3B.2, LED1.2, MH1.1, MH2.1, MH3.1, MH4.1, SW1.C, SW1.S2
LED_ANODE: LED1.1, R8.2
LED_GPIO: J1.8, J3.8, R8.1
OT_RX_SIG: J1.4, J2.12, J3.4
OT_TX_SIG: J1.3, J2.11, J3.3
SCL: J1.5, J3.5, J3B.3
SDA: J1.6, J3.6, J3B.4
